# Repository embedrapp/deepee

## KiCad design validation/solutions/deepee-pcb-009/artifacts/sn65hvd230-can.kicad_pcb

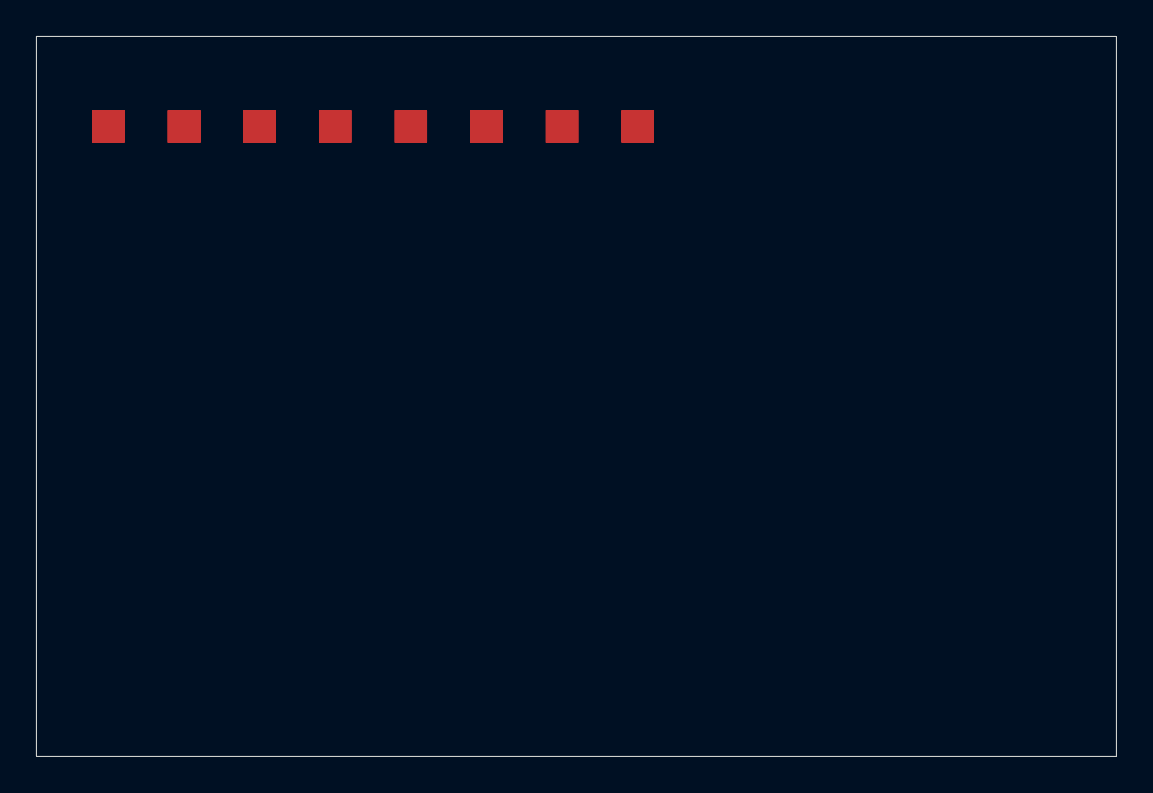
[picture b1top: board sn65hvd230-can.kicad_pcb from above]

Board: 2 copper layers, 60.0 x 40.0 mm, 6 parts (0 on the bottom side), 8 nets.

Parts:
C1: 100nF; C_0603_1608Metric
J1: Conn_01x05; PinHeader_1x05_P2.54mm_Vertical
J2: Conn_01x03; TerminalBlock_RND_205-00288_1x03_P5.08mm_Horizontal
R1: 120R; R_0603_1608Metric
R2: 10k; R_0603_1608Metric
U1: SN65HVD230; SOIC-8_3.9x4.9mm_P1.27mm

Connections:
3V3: C1.1, J1.1, U1.3
CANH: J2.1, R1.1, U1.7
CANL: J2.2, R1.2, U1.6
CAN_RX: J1.4, U1.4
CAN_TX: J1.3, U1.1
GND: C1.2, J1.2, J2.3, R2.2, U1.2
RS: R2.1, U1.8
VREF: J1.5, U1.5
